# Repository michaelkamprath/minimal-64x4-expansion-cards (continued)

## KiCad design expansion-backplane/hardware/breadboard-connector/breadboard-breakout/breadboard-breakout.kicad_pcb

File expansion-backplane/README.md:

# Expansion Backplane for Minimal 64x4 Computer

This backplane allows connecting of up to 4 expansion cards to the Minimal 64x4 computer. The [expansion connector](./hardware/expansion-connector/) is a convenient way to connect the backplane to the Minimal 64x4 computer.

### Shared `INH` Line
To have multiple cards connected to the backplane, they need to share the active high `INH` inhibit line. If multiple cards are emitting a LOW signal directly, and one emits a HIGH, contention will occur. To prevent such contention, the back plane uses a 74AHCT126 to arbitrate the `INH` signal's progression from a card to the Minimal 64x4's exansion port. Each of the buffers in the 74AHCT126 have their input signal tied high, and the each card's `INH` output us used to control the output enable for it's assigned buffer. In this way, when a card's `INH` output is low (not active), it's corresponding buffer has its output in a high-Z state. So if another card asserts it's `INH` line high, there won't be bus contention back to the card. But each card's active high `INH` signal is passed through to the Minimal 64x4. The downside is that each expansion card cannot monitor whether another card is asserting the `INH` signal. This is not deemed to be a signficant issues since Minimal 64x4 expansion board are generally memory mapped, and thus only one can be actively writing to the bus at a time.

### Card Address Assignment
The data bus has **no arbitration** — the `INH` scheme above protects only the inhibit line. Correctness depends entirely on one card decoding a given address. Because address lines settle at different times during a bus transition, a card can transiently match another card's address and drive the bus against it, so assign base addresses to maximize the **Hamming distance of the decoded address bits**, not the hex separation.

| Card | Base | Decoded `A7..A3` |
| --- | --- | --- |
| Multiplier | `$FED0` | `11010` |
| Timer | `$FE28` | `00101` |

**Failure signature** (seen 2026-08 with the timer at `$FEF0`, one bit from the multiplier): reads from the victim card return wrong values intermittently, writes and RAM are fine, results vary run to run *and* between builds as code shifts, and software-only builds are perfect. Diagnose by moving one card, not by debugging the software.

Two mechanisms produce this and are **not yet distinguished**: address-line skew, or the 74HCT688 comparator glitching its output during input transitions. If it's the latter, bit distance is only probabilistic protection and a gated `/G` or delayed enable is needed. To measure: reinstate the colliding address, run `multiplier/software/test_karatsuba_layers.min64x4` (fails ~30% of 65536 cases, so events are continuous), and trigger a logic analyzer on *the victim card's decode asserting while the address belongs to the other card*.

Note that CLK-gating a card's read output enable is **not** a fix: the address and `RI`/`RO` are set on the falling edge and the selected card must be driving the bus before the rising edge latches it, so the read enable has to be live during the settling window by design.

### Power Barrel Jack
The back plane provides a convenient standard 2.1 mm barrel jack you may use to connect to a regulated `5V` power supply to power the expansion cards and additionally power the Minimal 64x4 computer. If this barrel jack is connected to power, be sure to not connect the UART's `+5V` line to the Minimal 64x4 (still connect `GND`)

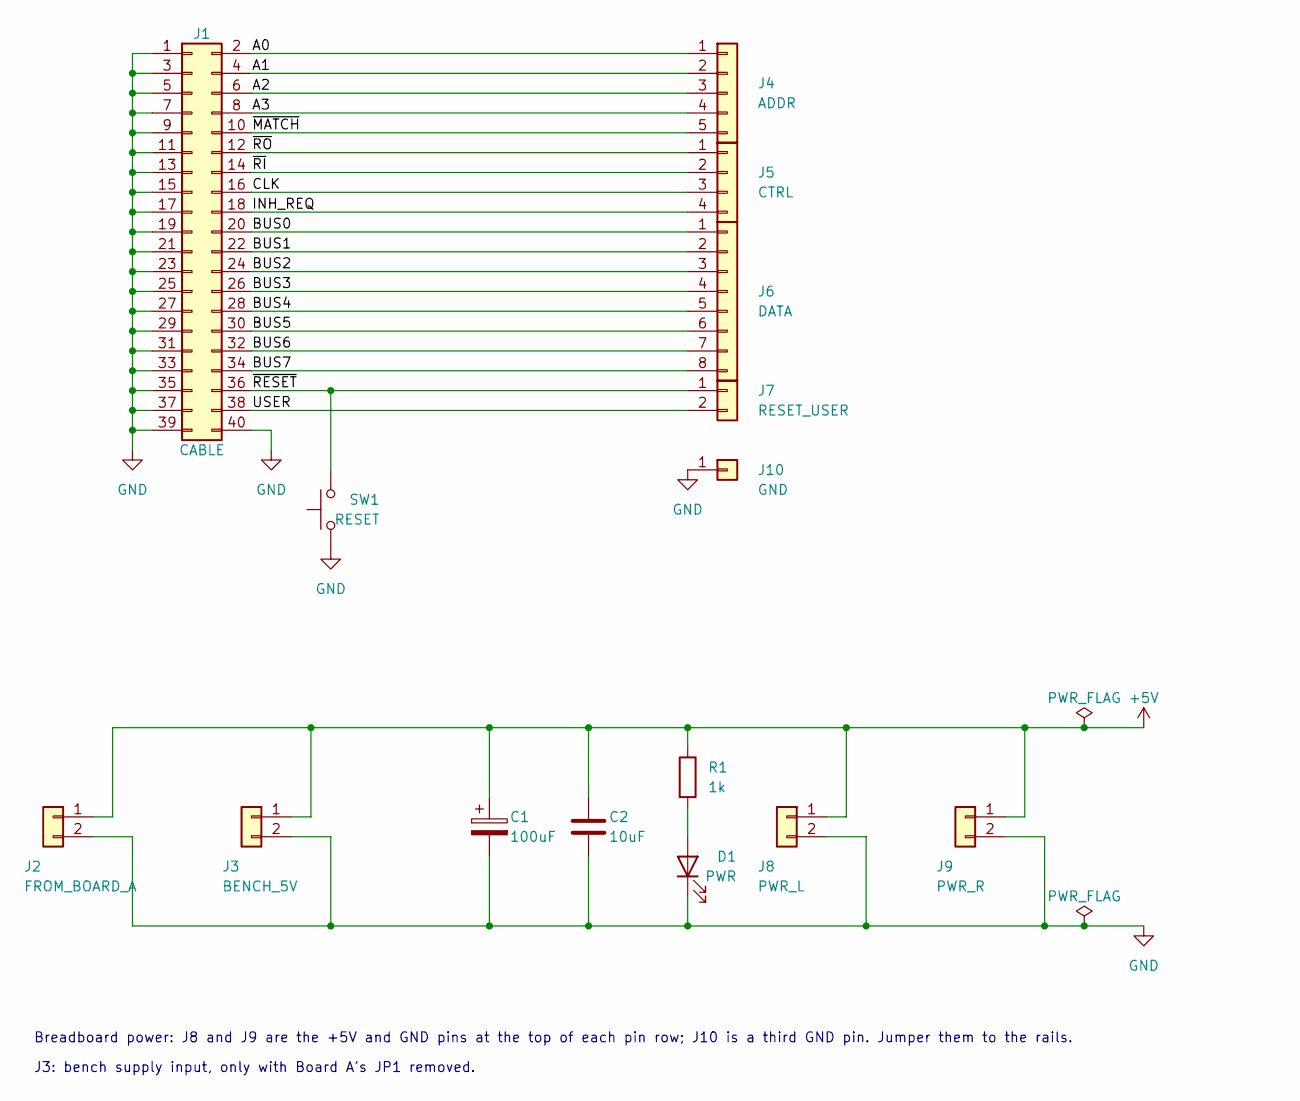
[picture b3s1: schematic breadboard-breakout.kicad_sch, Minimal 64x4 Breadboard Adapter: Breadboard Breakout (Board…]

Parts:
C1: 100uF; CP_Radial_D6.3mm_P2.50mm
C2: 10uF; C_Disc_D5.0mm_W2.5mm_P5.00mm
D1: PWR; LED_D3.0mm
J1: CABLE; IDC-Header_2x20_P2.54mm_Vertical; Manufacturer Part Number Sullins SBH11-PBPC-D20-ST-BK
J2: FROM_BOARD_A; TerminalBlock_Phoenix_MKDS-1,5-2-5.08_1x02_P5.08mm_Horizont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
J3: BENCH_5V; TerminalBlock_Phoenix_MKDS-1,5-2-5.08_1x02_P5.08mm_Horizont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
J4: ADDR; PinHeader_1x05_P2.54mm_Vertical
J5: CTRL; PinHeader_1x04_P2.54mm_Vertical
J6: DATA; PinHeader_1x08_P2.54mm_Vertical
J7: RESET_USER; PinHeader_1x02_P2.54mm_Vertical
J8: PWR_L; PinHeader_1x02_P2.54mm_Vertical
J9: PWR_R; PinHeader_1x02_P2.54mm_Vertical
J10: GND; PinHeader_1x01_P2.54mm_Vertical
R1: 1k; R_Axial_DIN0207_L6.3mm_D2.5mm_P7.62mm_Horizontal
SW1: RESET; SW_PUSH_6mm

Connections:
+5V: C1.1, C2.1, J2.1, J3.1, J8.1, J9.1, R1.1
/A0: J1.2, J4.1
/A1: J1.4, J4.2
/A2: J1.6, J4.3
/A3: J1.8, J4.4
/BUS0: J1.20, J6.1
/BUS1: J1.22, J6.2
/BUS2: J1.24, J6.3
/BUS3: J1.26, J6.4
/BUS4: J1.28, J6.5
/BUS5: J1.30, J6.6
/BUS6: J1.32, J6.7
/BUS7: J1.34, J6.8
/CLK: J1.16, J5.3
/INH_REQ: J1.18, J5.4
/USER: J1.38, J7.2
/~MATCH: J1.10, J4.5
/~RESET: J1.36, J7.1, SW1.2
/~RI: J1.14, J5.2
/~RO: J1.12, J5.1
GND: C1.2, C2.2, D1.1 (K), J1.1, J1.3, J1.5, J1.7, J1.9, J1.11, J1.13, J1.15, J1.17, J1.19, J1.21, J1.23, J1.25, J1.27, J1.29, J1.31, J1.33, J1.35, J1.37, J1.39, J1.40, J2.2, J3.2, J8.2, J9.2, J10.1, SW1.1
unnamed: D1.2 (A), R1.2

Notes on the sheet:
Breadboard power: J8 and J9 are the +5V and GND pins at the top of each pin row; J10 is a third GND pin. Jumper them to the rails.
J3: bench supply input, only with Board A's JP1 removed.

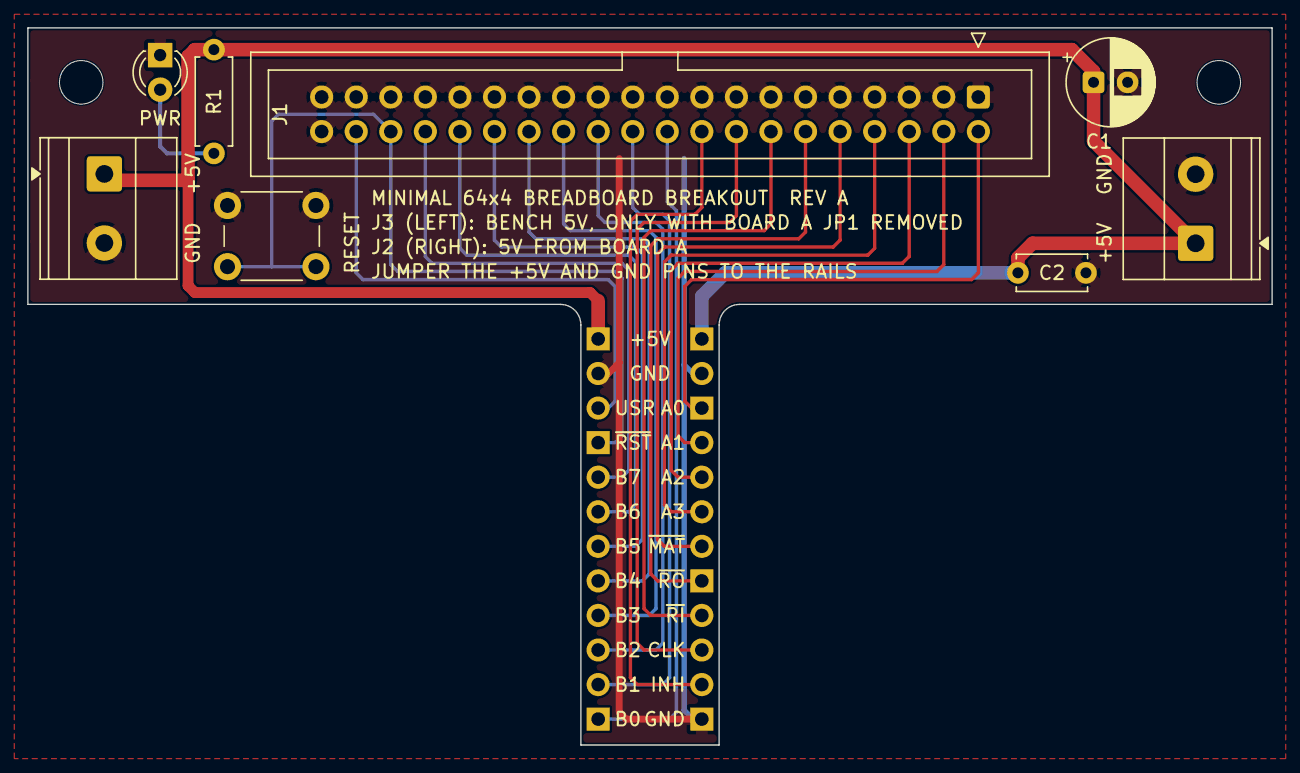
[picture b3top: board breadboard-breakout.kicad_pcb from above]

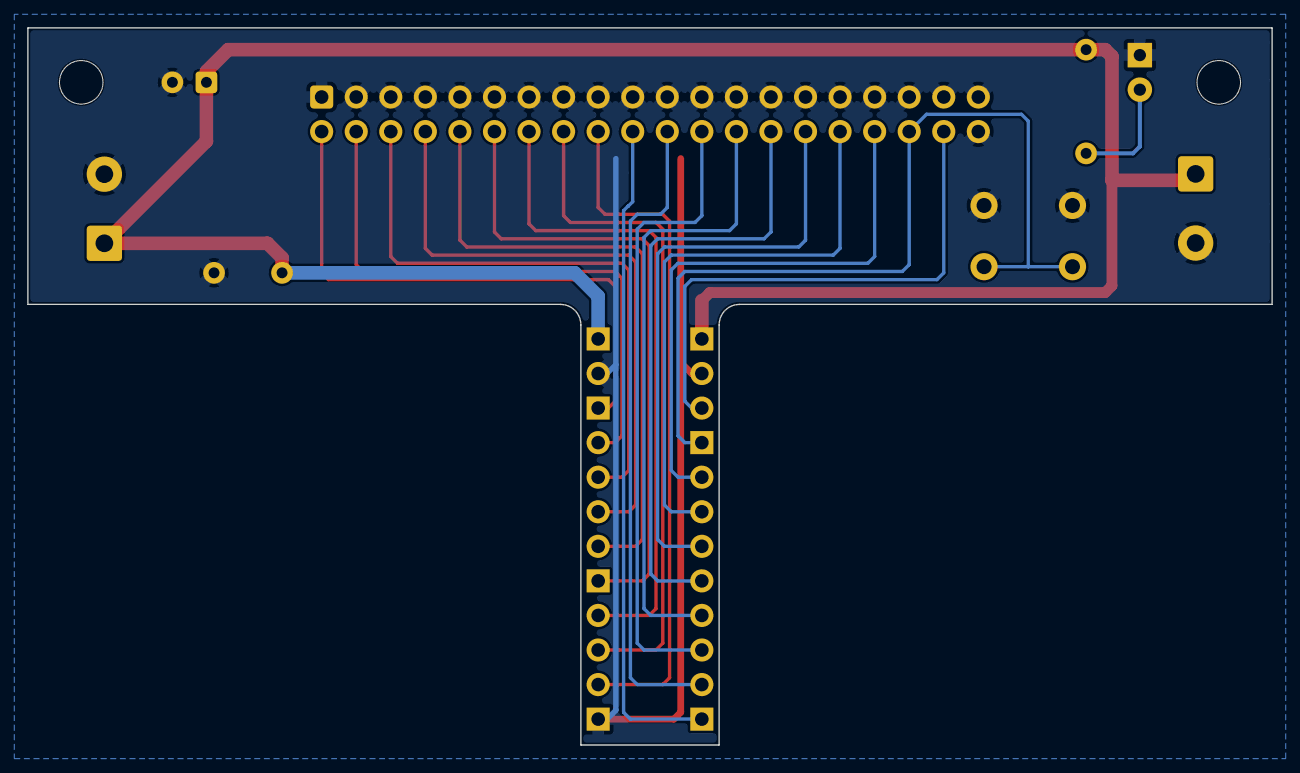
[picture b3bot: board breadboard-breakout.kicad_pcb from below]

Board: 2 copper layers, 91.4 x 52.7 mm, 17 parts (7 on the bottom side), 22 nets.

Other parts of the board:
H1, H2: M3; MountingHole_3.2mm_M3

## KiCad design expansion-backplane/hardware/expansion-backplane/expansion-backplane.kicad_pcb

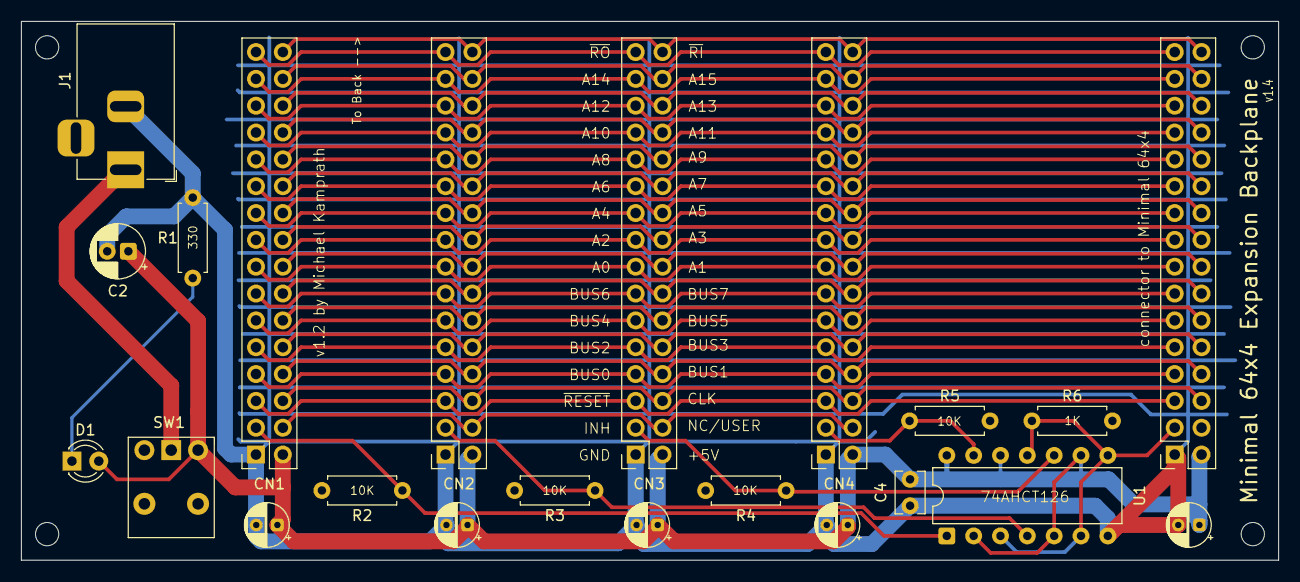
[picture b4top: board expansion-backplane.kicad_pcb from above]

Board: 2 copper layers, 119.0 x 51.0 mm, 22 parts (0 on the bottom side), 38 nets.

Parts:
C1, C3, C5, C6, C7: 1 µF; CP_Radial_D4.0mm_P2.00mm
C2: 10 µF; CP_Radial_D5.0mm_P2.00mm
C4: 0.1 uF; C_Disc_D3.8mm_W2.6mm_P2.50mm
CN1, CN2, CN3, CN4, CN5: PinSocket_2x16_P2.54mm_Vertical
D1: LED; LED_D3.0mm
J1: Barrel_Jack; BarrelJack_Horizontal
R1: 330; R_Axial_DIN0207_L6.3mm_D2.5mm_P7.62mm_Horizontal
R2, R3, R4, R5: 10K; R_Axial_DIN0207_L6.3mm_D2.5mm_P7.62mm_Horizontal
R6: 1K; R_Axial_DIN0207_L6.3mm_D2.5mm_P7.62mm_Horizontal
SW1: SW_SPDT; E-Switch_200MSP1T2B2M6RE
U1: 74AHCT126; DIP-14_W7.62mm

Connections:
+5V: C1.1, C2.1, C3.1, C4.1, C5.1, C6.1, C7.1, CN1.2 (+5V), CN2.2 (+5V), CN3.2 (+5V), CN4.2 (+5V), CN5.2 (+5V), D1.2 (A), SW1.1 (A), U1.2, U1.5, U1.9, U1.12, U1.14 (VCC)
A0: CN1.15 (A0), CN2.15 (A0), CN3.15 (A0), CN4.15 (A0), CN5.15 (A0)
A1: CN1.16 (A1), CN2.16 (A1), CN3.16 (A1), CN4.16 (A1), CN5.16 (A1)
A2: CN1.17 (A2), CN2.17 (A2), CN3.17 (A2), CN4.17 (A2), CN5.17 (A2)
A3: CN1.18 (A3), CN2.18 (A3), CN3.18 (A3), CN4.18 (A3), CN5.18 (A3)
A4: CN1.19 (A4), CN2.19 (A4), CN3.19 (A4), CN4.19 (A4), CN5.19 (A4)
A5: CN1.20 (A5), CN2.20 (A5), CN3.20 (A5), CN4.20 (A5), CN5.20 (A5)
A6: CN1.21 (A6), CN2.21 (A6), CN3.21 (A6), CN4.21 (A6), CN5.21 (A6)
A7: CN1.22 (A7), CN2.22 (A7), CN3.22 (A7), CN4.22 (A7), CN5.22 (A7)
A8: CN1.23 (A8), CN2.23 (A8), CN3.23 (A8), CN4.23 (A8), CN5.23 (A8)
A9: CN1.24 (A9), CN2.24 (A9), CN3.24 (A9), CN4.24 (A9), CN5.24 (A9)
A10: CN1.25 (A10), CN2.25 (A10), CN3.25 (A10), CN4.25 (A10), CN5.25 (A10)
A11: CN1.26 (A11), CN2.26 (A11), CN3.26 (A11), CN4.26 (A11), CN5.26 (A11)
A12: CN1.27 (A12), CN2.27 (A12), CN3.27 (A12), CN4.27 (A12), CN5.27 (A12)
A13: CN1.28 (A13), CN2.28 (A13), CN3.28 (A13), CN4.28 (A13), CN5.28 (A13)
A14: CN1.29 (A14), CN2.29 (A14), CN3.29 (A14), CN4.29 (A14), CN5.29 (A14)
A15: CN1.30 (A15), CN2.30 (A15), CN3.30 (A15), CN4.30 (A15), CN5.30 (A15)
BUS0: CN1.7 (BUS0), CN2.7 (BUS0), CN3.7 (BUS0), CN4.7 (BUS0), CN5.7 (BUS0)
BUS1: CN1.8 (BUS1), CN2.8 (BUS1), CN3.8 (BUS1), CN4.8 (BUS1), CN5.8 (BUS1)
BUS2: CN1.9 (BUS2), CN2.9 (BUS2), CN3.9 (BUS2), CN4.9 (BUS2), CN5.9 (BUS2)
BUS3: CN1.10 (BUS3), CN2.10 (BUS3), CN3.10 (BUS3), CN4.10 (BUS3), CN5.10 (BUS3)
BUS4: CN1.11 (BUS4), CN2.11 (BUS4), CN3.11 (BUS4), CN4.11 (BUS4), CN5.11 (BUS4)
BUS5: CN1.12 (BUS5), CN2.12 (BUS5), CN3.12 (BUS5), CN4.12 (BUS5), CN5.12 (BUS5)
BUS6: CN1.13 (BUS6), CN2.13 (BUS6), CN3.13 (BUS6), CN4.13 (BUS6), CN5.13 (BUS6)
BUS7: CN1.14 (BUS7), CN2.14 (BUS7), CN3.14 (BUS7), CN4.14 (BUS7), CN5.14 (BUS7)
CLK: CN1.6 (CLK), CN2.6 (CLK), CN3.6 (CLK), CN4.6 (CLK), CN5.6 (CLK)
GND: C1.2, C2.2, C3.2, C4.2, C5.2, C6.2, C7.2, CN1.1 (GND), CN2.1 (GND), CN3.1 (GND), CN4.1 (GND), CN5.1 (GND), J1.2, R1.2, R2.2, R3.2, R4.2, R5.2, R6.2, U1.7 (GND)
unnamed: CN1.3 (INH), R2.1, U1.1
unnamed: CN2.3 (INH), R3.1, U1.4
unnamed: CN3.3 (INH), R4.1, U1.10
unnamed: CN4.3 (INH), R5.1, U1.13
unnamed: CN5.3 (INH), R6.1, U1.3, U1.6, U1.8, U1.11
unnamed: D1.1 (K), R1.1
unnamed: J1.1, SW1.2 (B)
USER: CN1.4 (NC), CN2.4 (NC), CN3.4 (NC), CN4.4 (NC)
~RESET: CN1.5 (~RESET), CN2.5 (~RESET), CN3.5 (~RESET), CN4.5 (~RESET), CN5.5 (~RESET)
~RI: CN1.32 (~RI), CN2.32 (~RI), CN3.32 (~RI), CN4.32 (~RI), CN5.32 (~RI)
~RO: CN1.31 (~RO), CN2.31 (~RO), CN3.31 (~RO), CN4.31 (~RO), CN5.31 (~RO)

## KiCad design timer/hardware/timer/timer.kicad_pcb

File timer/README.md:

# Timer - Clock Counter
This Timer card provides a convenient way to capture precise timing on the Minimal 64x4 by counting clock cycles. The counter is resettable to 0, allowing specific operations to be timed. The counter is 48 bits wide, which allows time ranges up to about 1.1 years at the Minimal 64x4's 8 MHz clock frequency.

## Hardware Design
[This card](./hardware/) uses six 74HC590 8-bit counters arranged in a cascading carry chain to create a 48-bit counter. The 74HC590 has tri-state outputs, so each counter IC is connected directly to the data bus and remains in high-Z unless selected to drive its latched value. Card control is handled by two 74HC688 comparators (address decode) and an ATF22V10C programmable logic device (control logic for read byte select, latch, and reset). The combinational logic is captured in [the PLD code](./pld-files/).

## Memory Map

Define:

`base = $FE00 + (x << 4) + y`

Where:
- `y` is controlled by jumper `J1` (address bit A3): `J1` open => `y = 0`, `J1` bridged => `y = 8`.
- `x` is controlled by jumpers `J2`-`J5` (address bits A4-A7): `J2` is A4 (LSB of `x`) and `J5` is A7 (MSB of `x`).
- Jumpers are named from the PCB silkscreen (`J1`-`J5`).

| Offset From `base` | R/W   | Function       | Description |
| ------------------ | ----- | -------------- | ----------- |
| `+0`               | Read  | Latched Byte 0 | Read latched counter value, byte 0 (LSB) |
| `+1`               | Read  | Latched Byte 1 | Read latched counter value, byte 1 |
| `+2`               | Read  | Latched Byte 2 | Read latched counter value, byte 2 |
| `+3`               | Read  | Latched Byte 3 | Read latched counter value, byte 3 |
| `+4`               | Read  | Latched Byte 4 | Read latched counter value, byte 4 |
| `+5`               | Read  | Latched Byte 5 | Read latched counter value, byte 5 (MSB) |
| `+6`               | Write | Latch Counter  | Latch (snapshot) the current 48-bit counter into the output registers. Any value may be written to trigger this action. |
| `+7`               | Write | Reset Counter  | Reset the counter value to `0`. Any value may be written to trigger this action. |

Concrete ranges for a selected `x`:
- `J1` open (`y = 0`): registers are at `$FEx0`-`$FEx7`.
- `J1` bridged (`y = 8`): registers are at `$FEx8`-`$FExF`.

Notes:
- Bridging all jumpers `J2` through `J5` sets `x` to `$F`; leaving them open sets `x` to `$0` (default).
- Reading `$FEx0`-`$FEx5` (or `$FEx8`-`$FExD` when `J1` is bridged) returns the last value latched by writing to the latch register, not necessarily the current counter value.
- Resetting the counter does not latch a `0` value.

### Default Jumper Setttings
The code in this repo assumes the timer card's base address is $FE28. This is accomplished by jumpering J1 and J3, and leaving the others open.

## Time Range
This card has a 48-bit counter that is read one byte at a time. Not all bytes need to be read, but reading fewer bytes reduces the effective time range captured. At the **Minimal 64x4**'s 8 MHz clock, the maximum time range by number of bytes read is shown in this table:

| Bytes | Bits | Max Seconds (s) | Approx Time                      |
| ----: | ---: | --------------: | -------------------------------- |
|     6 |   48 | 35184372.088832 | 407.22652996 days (~1.115 years) |
|     5 |   40 |   137438.953472 | 38.17748708 hours (~1.5907 days) |
|     4 |   32 |      536.870912 | 8.94784853 minutes               |
|     3 |   24 |        2.097152 | 2.097152 seconds                 |
|     2 |   16 |        0.008192 | 8.192 ms                         |
|     1 |    8 |        0.000032 | 32 µs                            |

The latched bytes are arranged in little-endian order: `base + 0` is the LSB and `base + 5` is the MSB.

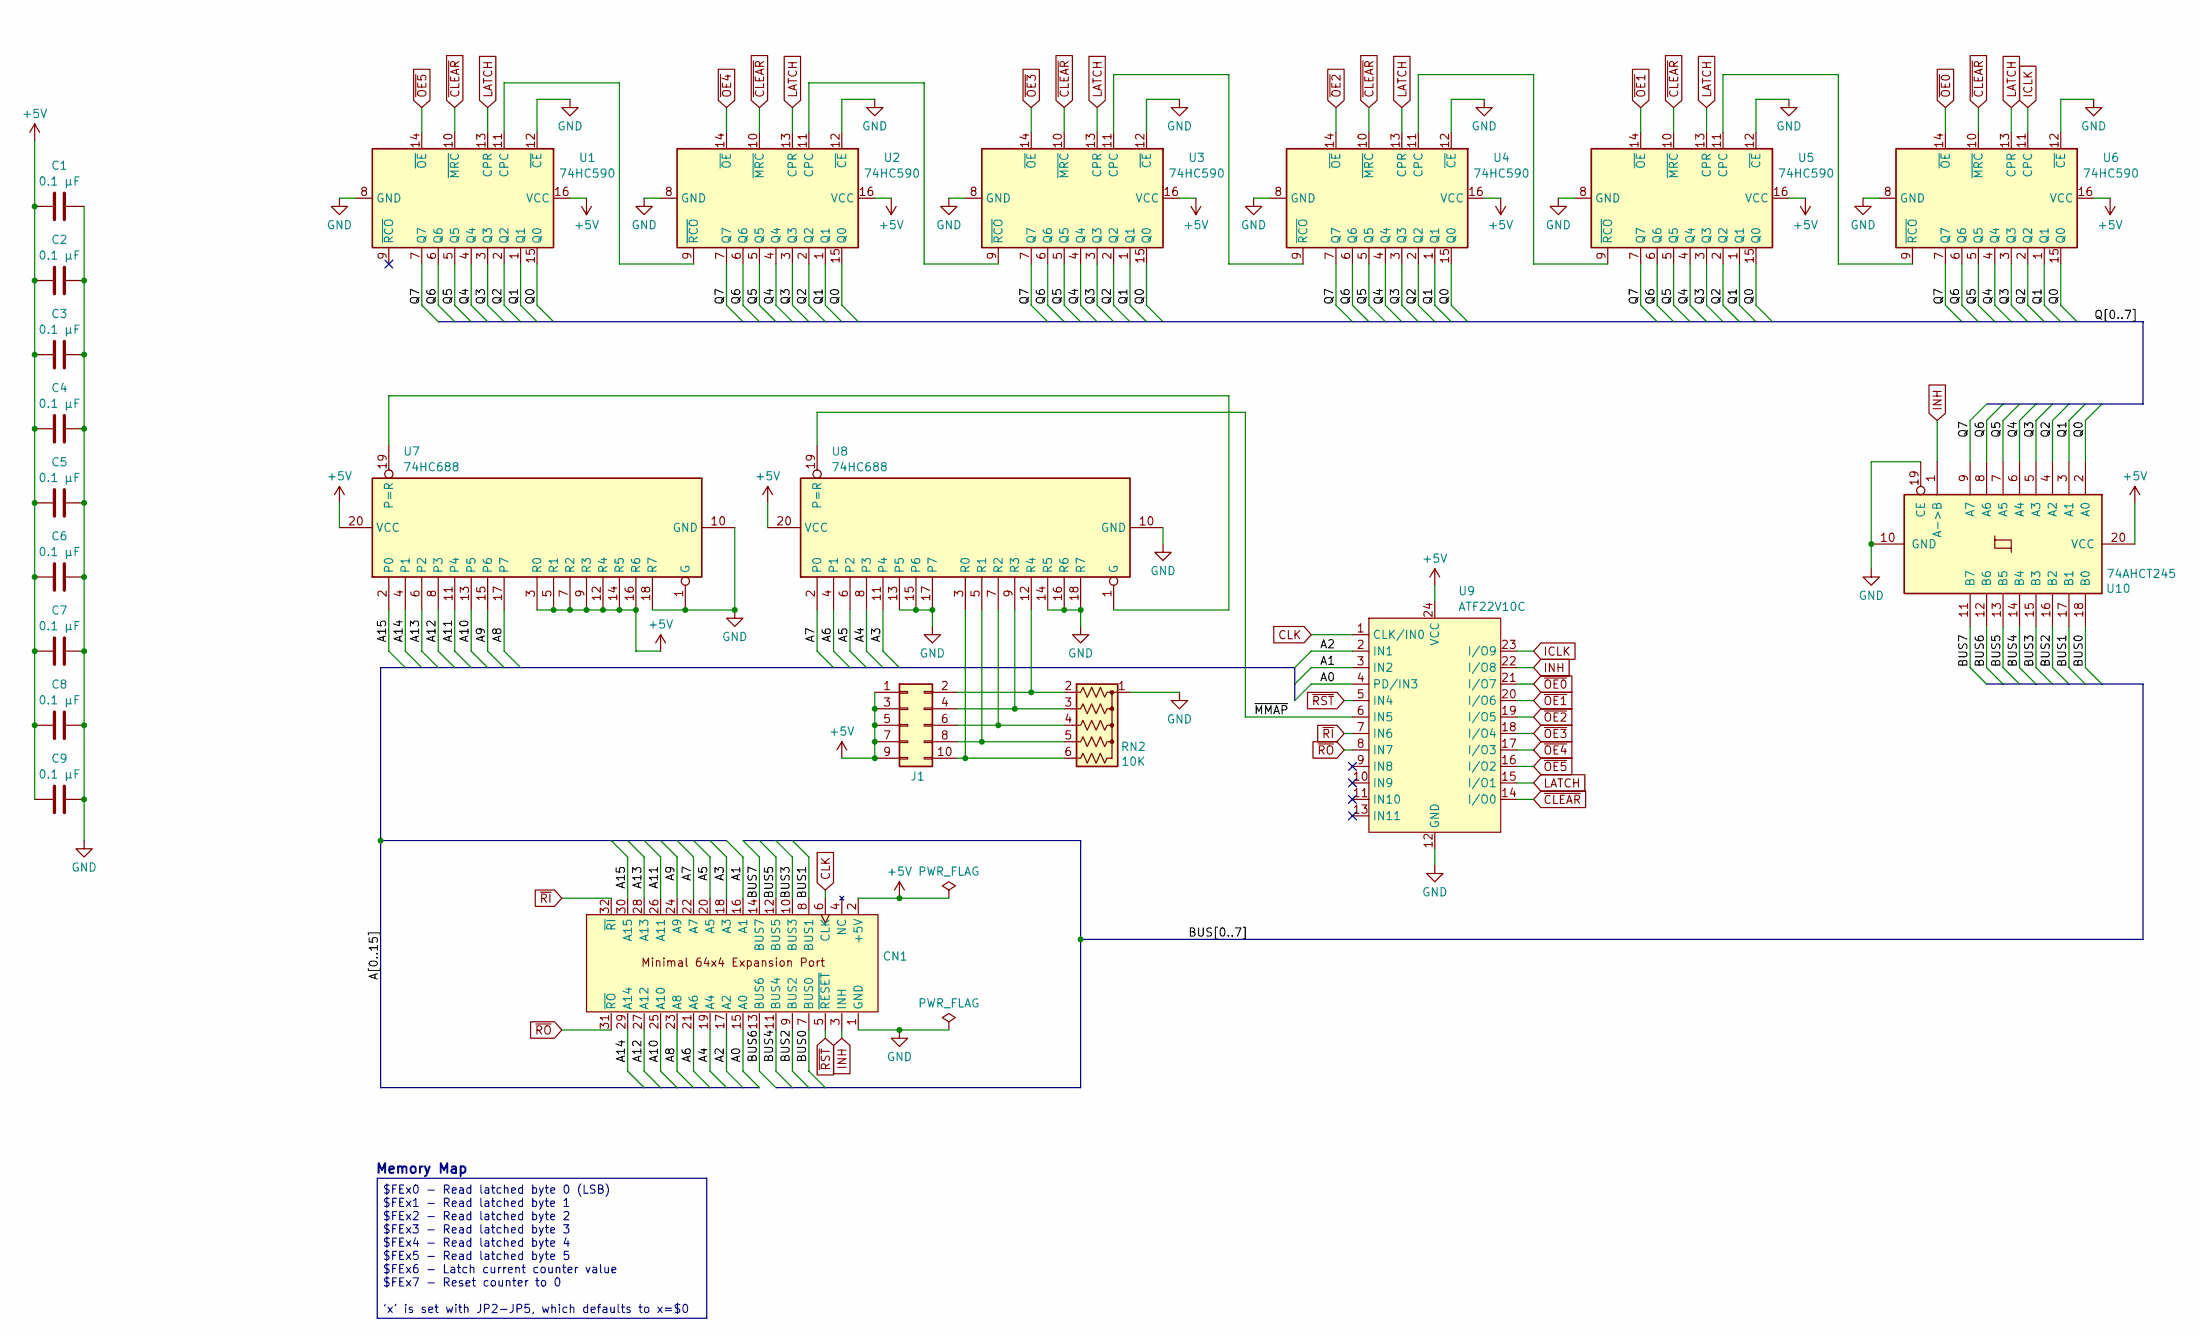
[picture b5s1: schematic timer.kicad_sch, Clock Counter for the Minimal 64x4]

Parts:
C1, C2, C3, C4, C5, C6, C7, C8, C9: 0.1 µF; C_Disc_D3.4mm_W2.1mm_P2.50mm
CN1: PinHeader_2x16_P2.54mm_Horizontal
J1: Conn_02x05_Odd_Even; PinHeader_2x05_P2.54mm_Vertical
RN2: 10K; R_Array_SIP6
U1, U2, U3, U4, U5, U6: 74HC590; DIP-16_W7.62mm_Socket
U7, U8: 74HC688; DIP-20_W7.62mm_Socket
U9: ATF22V10C; DIP-24_W7.62mm_Socket
U10: 74AHCT245; DIP-20_W7.62mm_Socket

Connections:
+5V: C1.1, C2.1, C3.1, C4.1, C5.1, C6.1, C7.1, C8.1, C9.1, CN1.2 (+5V), J1.1, J1.3, J1.5, J1.7, J1.9, U1.16 (VCC), U2.16 (VCC), U3.16 (VCC), U4.16 (VCC), U5.16 (VCC), U6.16 (VCC), U7.3 (R0), U7.5 (R1), U7.7 (R2), U7.9 (R3), U7.12 (R4), U7.14 (R5), U7.16 (R6), U7.20 (VCC), U8.20 (VCC), U9.24 (VCC), U10.20 (VCC)
/A0: CN1.15 (A0), U9.4 (PD/IN3)
/A1: CN1.16 (A1), U9.3 (IN2)
/A2: CN1.17 (A2), U9.2 (IN1)
/A3: CN1.18 (A3), U8.11 (P4)
/A4: CN1.19 (A4), U8.8 (P3)
/A5: CN1.20 (A5), U8.6 (P2)
/A6: CN1.21 (A6), U8.4 (P1)
/A7: CN1.22 (A7), U8.2 (P0)
/A8: CN1.23 (A8), U7.17 (P7)
/A9: CN1.24 (A9), U7.15 (P6)
/A10: CN1.25 (A10), U7.13 (P5)
/A11: CN1.26 (A11), U7.11 (P4)
/A12: CN1.27 (A12), U7.8 (P3)
/A13: CN1.28 (A13), U7.6 (P2)
/A14: CN1.29 (A14), U7.4 (P1)
/A15: CN1.30 (A15), U7.2 (P0)
/BUS0: CN1.7 (BUS0), U10.18 (B0)
/BUS1: CN1.8 (BUS1), U10.17 (B1)
/BUS2: CN1.9 (BUS2), U10.16 (B2)
/BUS3: CN1.10 (BUS3), U10.15 (B3)
/BUS4: CN1.11 (BUS4), U10.14 (B4)
/BUS5: CN1.12 (BUS5), U10.13 (B5)
/BUS6: CN1.13 (BUS6), U10.12 (B6)
/BUS7: CN1.14 (BUS7), U10.11 (B7)
/Q0: U1.15 (Q0), U2.15 (Q0), U3.15 (Q0), U4.15 (Q0), U5.15 (Q0), U6.15 (Q0), U10.2 (A0)
/Q1: U1.1 (Q1), U2.1 (Q1), U3.1 (Q1), U4.1 (Q1), U5.1 (Q1), U6.1 (Q1), U10.3 (A1)
/Q2: U1.2 (Q2), U2.2 (Q2), U3.2 (Q2), U4.2 (Q2), U5.2 (Q2), U6.2 (Q2), U10.4 (A2)
/Q3: U1.3 (Q3), U2.3 (Q3), U3.3 (Q3), U4.3 (Q3), U5.3 (Q3), U6.3 (Q3), U10.5 (A3)
/Q4: U1.4 (Q4), U2.4 (Q4), U3.4 (Q4), U4.4 (Q4), U5.4 (Q4), U6.4 (Q4), U10.6 (A4)
/Q5: U1.5 (Q5), U2.5 (Q5), U3.5 (Q5), U4.5 (Q5), U5.5 (Q5), U6.5 (Q5), U10.7 (A5)
/Q6: U1.6 (Q6), U2.6 (Q6), U3.6 (Q6), U4.6 (Q6), U5.6 (Q6), U6.6 (Q6), U10.8 (A6)
/Q7: U1.7 (Q7), U2.7 (Q7), U3.7 (Q7), U4.7 (Q7), U5.7 (Q7), U6.7 (Q7), U10.9 (A7)
/~MMAP: U8.19 (P=R), U9.6 (IN5)
CLK: CN1.6 (CLK), U9.1 (CLK/IN0)
GND: C1.2, C2.2, C3.2, C4.2, C5.2, C6.2, C7.2, C8.2, C9.2, CN1.1 (GND), RN2.1 (common), U1.8 (GND), U1.12 (~CE), U2.8 (GND), U2.12 (~CE), U3.8 (GND), U3.12 (~CE), U4.8 (GND), U4.12 (~CE), U5.8 (GND), U5.12 (~CE), U6.8 (GND), U6.12 (~CE), U7.1 (G), U7.10 (GND), U7.18 (R7), U8.10 (GND), U8.13 (P5), U8.14 (R5), U8.15 (P6), U8.16 (R6), U8.17 (P7), U8.18 (R7), U9.12 (GND), U10.10 (GND), U10.19 (CE)
ICLK: U6.11 (CPC), U9.23 (I/O9)
INH: CN1.3 (INH), U9.22 (I/O8), U10.1 (A->B)
LATCH: U1.13 (CPR), U2.13 (CPR), U3.13 (CPR), U4.13 (CPR), U5.13 (CPR), U6.13 (CPR), U9.15 (I/O1)
unnamed: J1.2, RN2.2 (R1), U8.12 (R4)
unnamed: J1.4, RN2.3 (R2), U8.9 (R3)
unnamed: J1.6, RN2.4 (R3), U8.7 (R2)
unnamed: J1.8, RN2.5 (R4), U8.5 (R1)
unnamed: J1.10, RN2.6 (R5), U8.3 (R0)
unnamed: U1.11 (CPC), U2.9 (~RCO)
unnamed: U2.11 (CPC), U3.9 (~RCO)
unnamed: U3.11 (CPC), U4.9 (~RCO)
unnamed: U4.11 (CPC), U5.9 (~RCO)
unnamed: U5.11 (CPC), U6.9 (~RCO)
unnamed: U7.19 (P=R), U8.1 (G)
~CLEAR: U1.10 (~MRC), U2.10 (~MRC), U3.10 (~MRC), U4.10 (~MRC), U5.10 (~MRC), U6.10 (~MRC), U9.14 (I/O0)
~OE0: U6.14 (~OE), U9.21 (I/O7)
~OE1: U5.14 (~OE), U9.20 (I/O6)
~OE2: U4.14 (~OE), U9.19 (I/O5)
~OE3: U3.14 (~OE), U9.18 (I/O4)
~OE4: U2.14 (~OE), U9.17 (I/O3)
~OE5: U1.14 (~OE), U9.16 (I/O2)
~RI: CN1.32 (~RI), U9.7 (IN6)
~RO: CN1.31 (~RO), U9.8 (IN7)
~RST: CN1.5 (~RESET), U9.5 (IN4)

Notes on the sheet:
$FEx0 - Read latched byte 0 (LSB) $FEx1 - Read latched byte 1 $FEx2 - Read latched byte 2 $FEx3 - Read latched byte 3 $FEx4 - Read latched byte 4 $FEx5 - Read latched byte 5 $FEx6 - Latch current counter value $FEx7 - Reset counter to 0 'x' is set with JP2-JP5, which defaults to x=$0
Memory Map

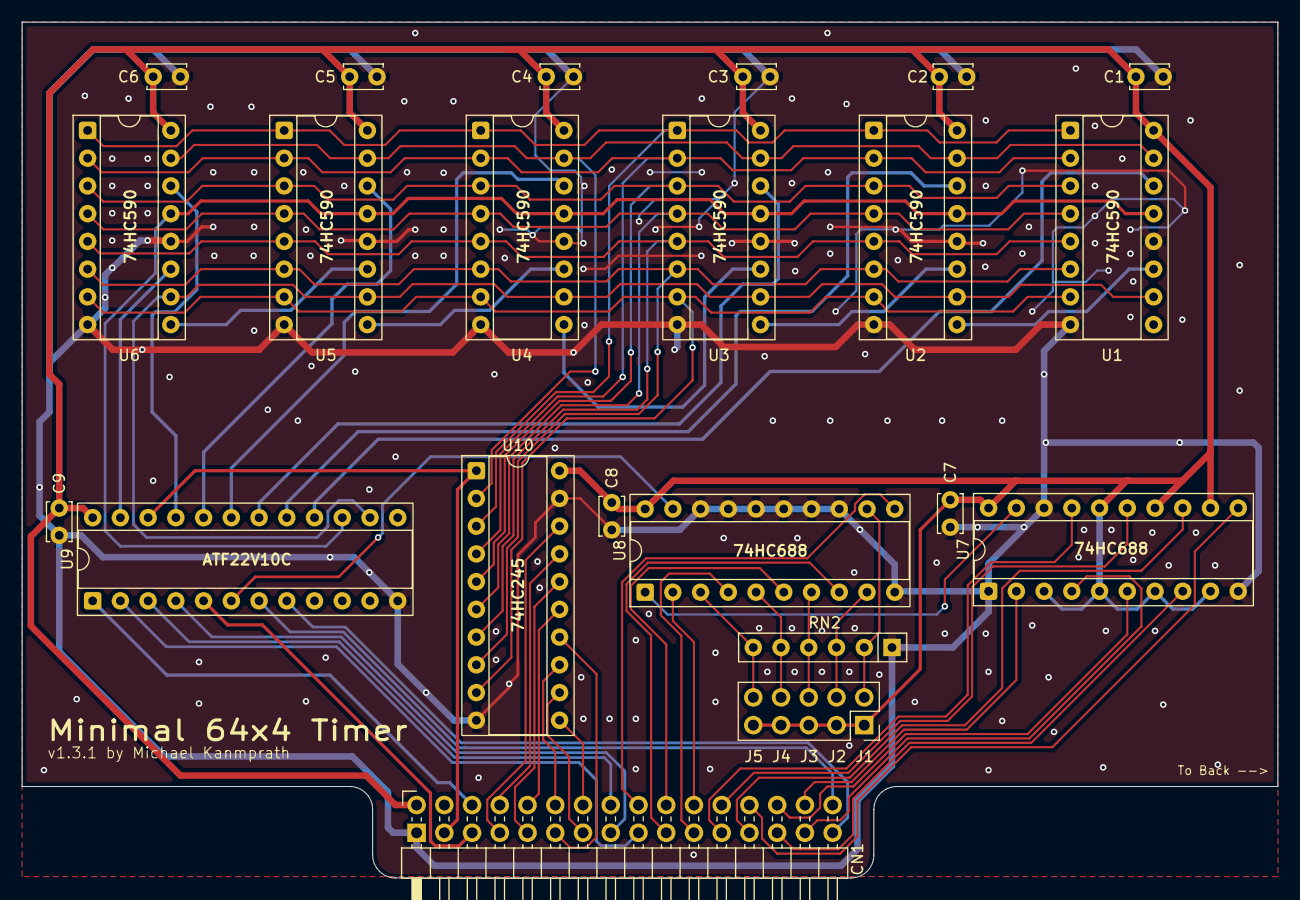
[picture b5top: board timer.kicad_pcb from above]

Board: 2 copper layers, 115.0 x 78.4 mm, 22 parts (0 on the bottom side), 60 nets.
